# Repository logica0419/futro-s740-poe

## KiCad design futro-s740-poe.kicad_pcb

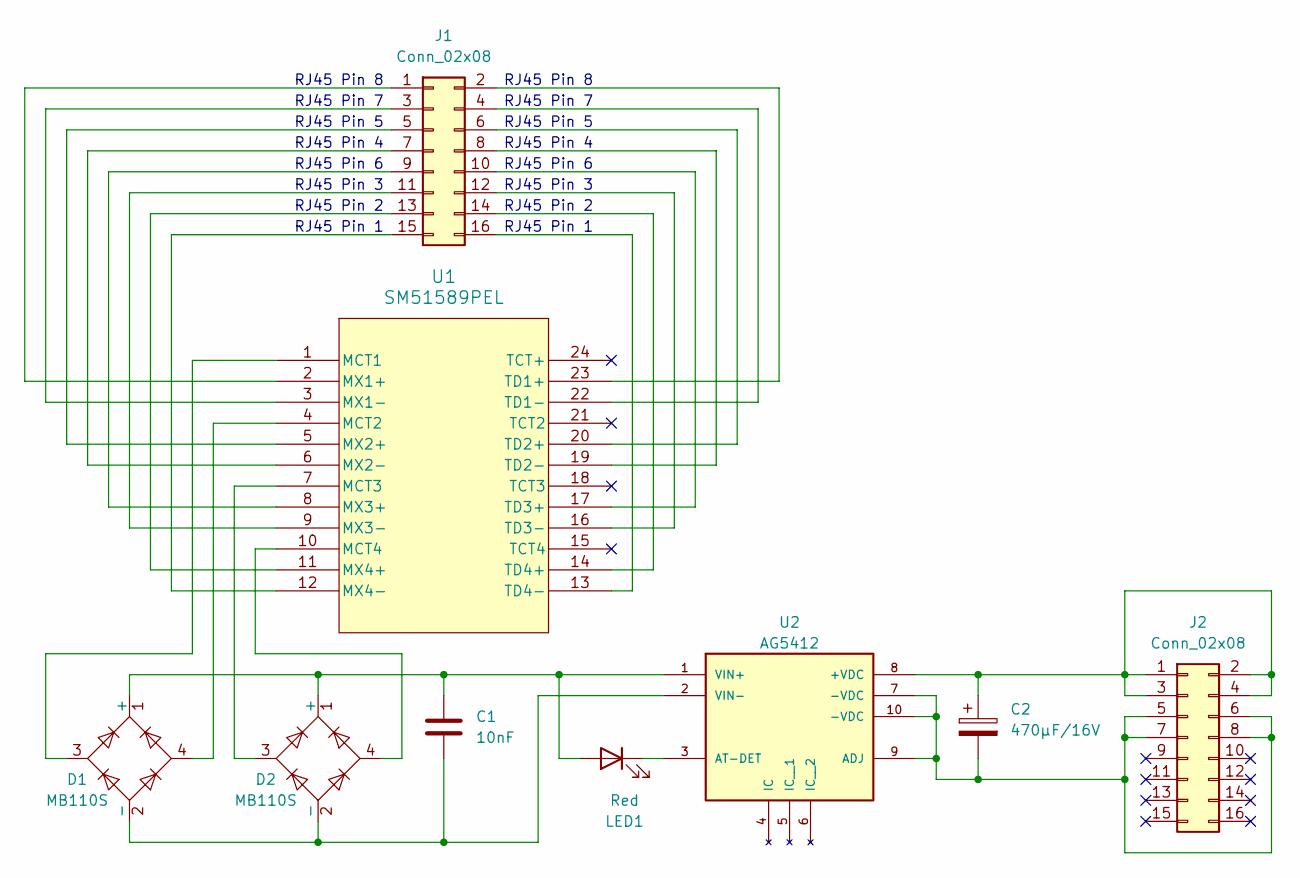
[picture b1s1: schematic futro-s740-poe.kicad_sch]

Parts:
C1: 10nF; C_1206_3216Metric
C2: 470μF/16V; CP_Radial_D8.0mm_P3.50mm
D1, D2: MB110S; TO-269AA
J1, J2: Conn_02x08; PinSocket_2x08_P2.00mm_Vertical_SMD
LED1: Red; LED_0805_2012Metric
U1: SM51589PEL
U2: AG5412; PARTREV V1.3; DigiKey_Part_Number 5061-AG5412-ND

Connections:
unnamed: C1.1, D1.1 (+), D2.1 (+), LED1.2 (A), U2.1 (VIN+)
unnamed: C1.2, D1.2 (-), D2.2 (-), U2.2 (VIN-)
unnamed: J1.1, U1.2 (MX1+)
unnamed: J1.2, U1.23 (TD1+)
unnamed: J1.3, U1.3 (MX1-)
unnamed: J1.4, U1.22 (TD1-)
unnamed: J1.5, U1.5 (MX2+)
unnamed: J1.6, U1.20 (TD2+)
unnamed: J1.7, U1.6 (MX2-)
unnamed: J1.8, U1.19 (TD2-)
unnamed: J1.9, U1.8 (MX3+)
unnamed: J1.10, U1.17 (TD3+)
unnamed: J1.11, U1.9 (MX3-)
unnamed: J1.12, U1.16 (TD3-)
unnamed: J1.13, U1.11 (MX4+)
unnamed: J1.14, U1.14 (TD4+)
unnamed: J1.15, U1.12 (MX4-)
unnamed: J1.16, U1.13 (TD4-)
unnamed: C2.1, J2.1, J2.2, J2.3, J2.4, U2.8 (+VDC)
unnamed: C2.2, J2.5, J2.6, J2.7, J2.8, U2.7 (-VDC), U2.9 (ADJ), U2.10 (-VDC)
unnamed: LED1.1 (K), U2.3 (AT-DET)
unnamed: D1.3, U1.1 (MCT1)
unnamed: D1.4, U1.4 (MCT2)
unnamed: D2.3, U1.7 (MCT3)
unnamed: D2.4, U1.10 (MCT4)

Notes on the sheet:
RJ45 Pin 8
RJ45 Pin 1
RJ45 Pin 5
RJ45 Pin 6
RJ45 Pin 2
RJ45 Pin 4
RJ45 Pin 7
RJ45 Pin 3

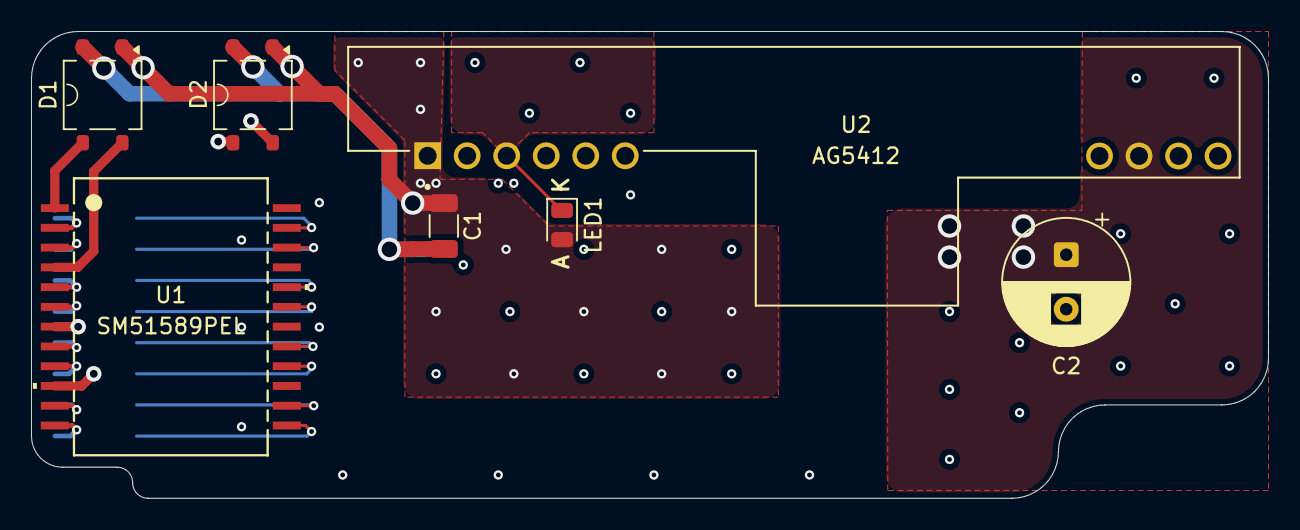
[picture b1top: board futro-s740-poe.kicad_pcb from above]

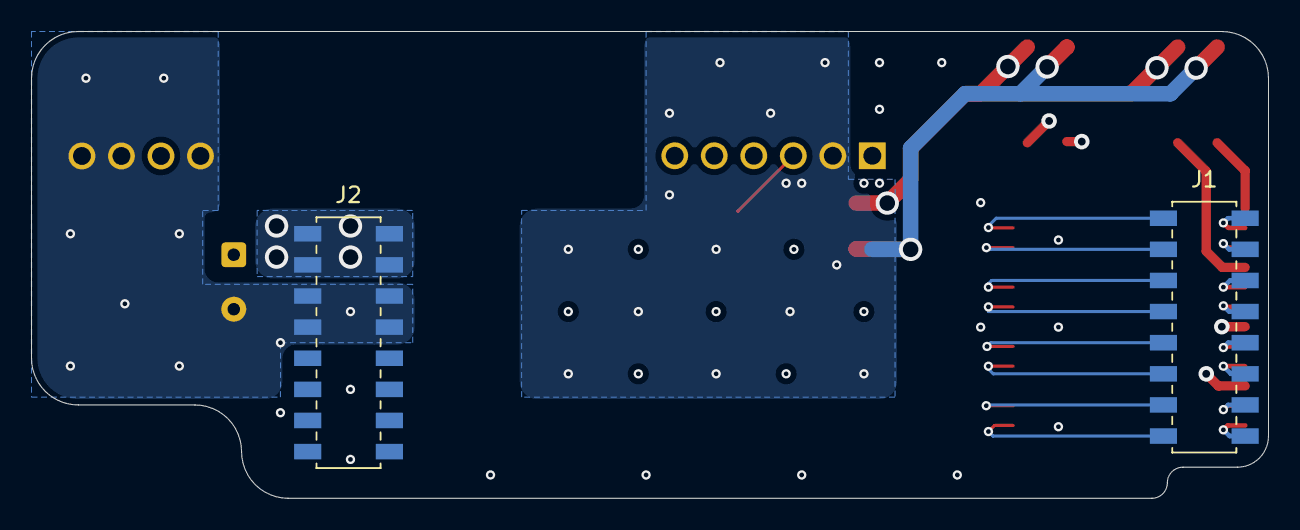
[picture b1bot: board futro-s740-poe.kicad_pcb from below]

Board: 4 copper layers, 79.5 x 30.0 mm, 9 parts (2 on the bottom side), 25 nets.
